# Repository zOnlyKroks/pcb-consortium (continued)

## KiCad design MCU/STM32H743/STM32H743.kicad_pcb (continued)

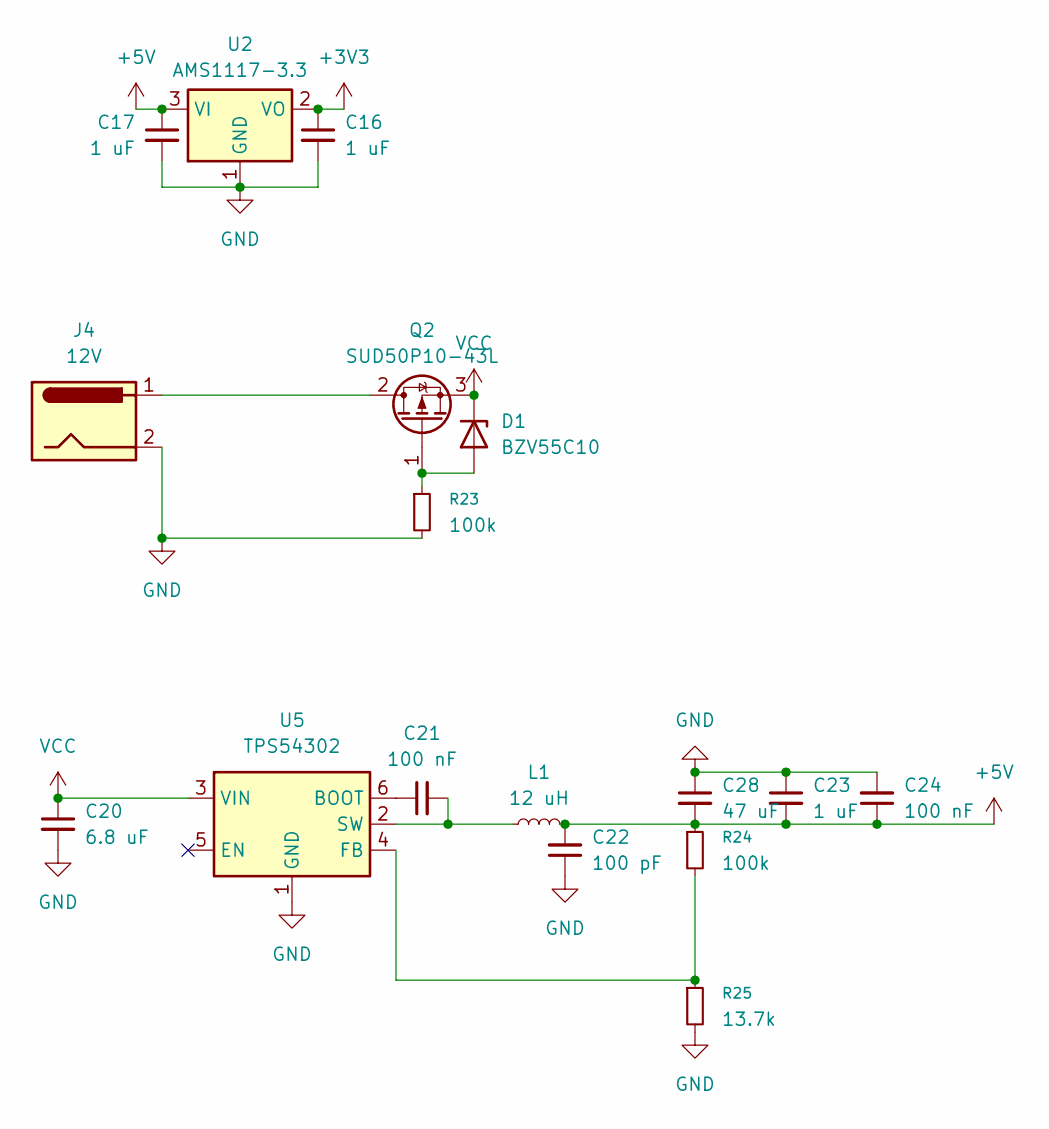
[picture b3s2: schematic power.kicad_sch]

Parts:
C16, C17, C23: 1 uF; C_0402_1005Metric
C20: 6.8 uF; C_0805_2012Metric
C21, C24: 100 nF; C_0402_1005Metric
C22: 100 pF; C_0402_1005Metric
C28: 47 uF; C_1206_3216Metric
D1: BZV55C10; D_MiniMELF
J4: 12V; BarrelJack_CUI_PJ-063AH_Horizontal
L1: 12 uH; L_0805_2012Metric
Q2: SUD50P10-43L; TO-252-2
R23, R24: 100k; R_0603_1608Metric
R25: 13.7k; R_0603_1608Metric
U2: AMS1117-3.3; SOT-223-3_TabPin2
U5: TPS54302; SOT-23-6

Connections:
+3V3: C16.1, U2.2 (VO); also elsewhere on the board
+5V: C17.1, C22.2, C23.2, C24.1, C28.2, L1.2, R24.1, U2.3 (VI); also elsewhere on the board
GND: C16.2, C17.2, C20.2, C22.1, C23.1, C24.2, C28.1, J4.2, R23.2, R25.2, U2.1 (GND), U5.1 (GND); also elsewhere on the board
unnamed: D1.2 (A), Q2.1 (G), R23.1
unnamed: J4.1, Q2.2 (D)
unnamed: C21.1, U5.6 (BOOT)
unnamed: R24.2, R25.1, U5.4 (FB)
unnamed: C21.2, L1.1, U5.2 (SW)
VCC: C20.1, D1.1 (K), Q2.3 (S), U5.3 (VIN)

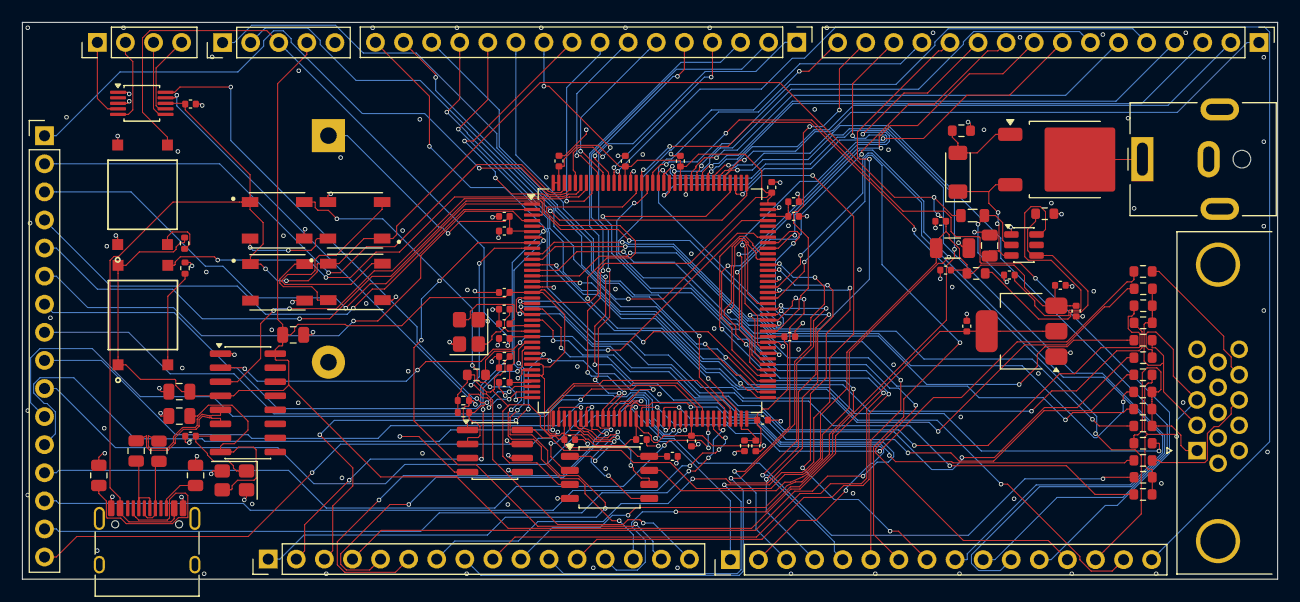
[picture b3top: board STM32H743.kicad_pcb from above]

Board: 4 copper layers, 113.5 x 50.3 mm, 91 parts (1 on the bottom side), 145 nets.

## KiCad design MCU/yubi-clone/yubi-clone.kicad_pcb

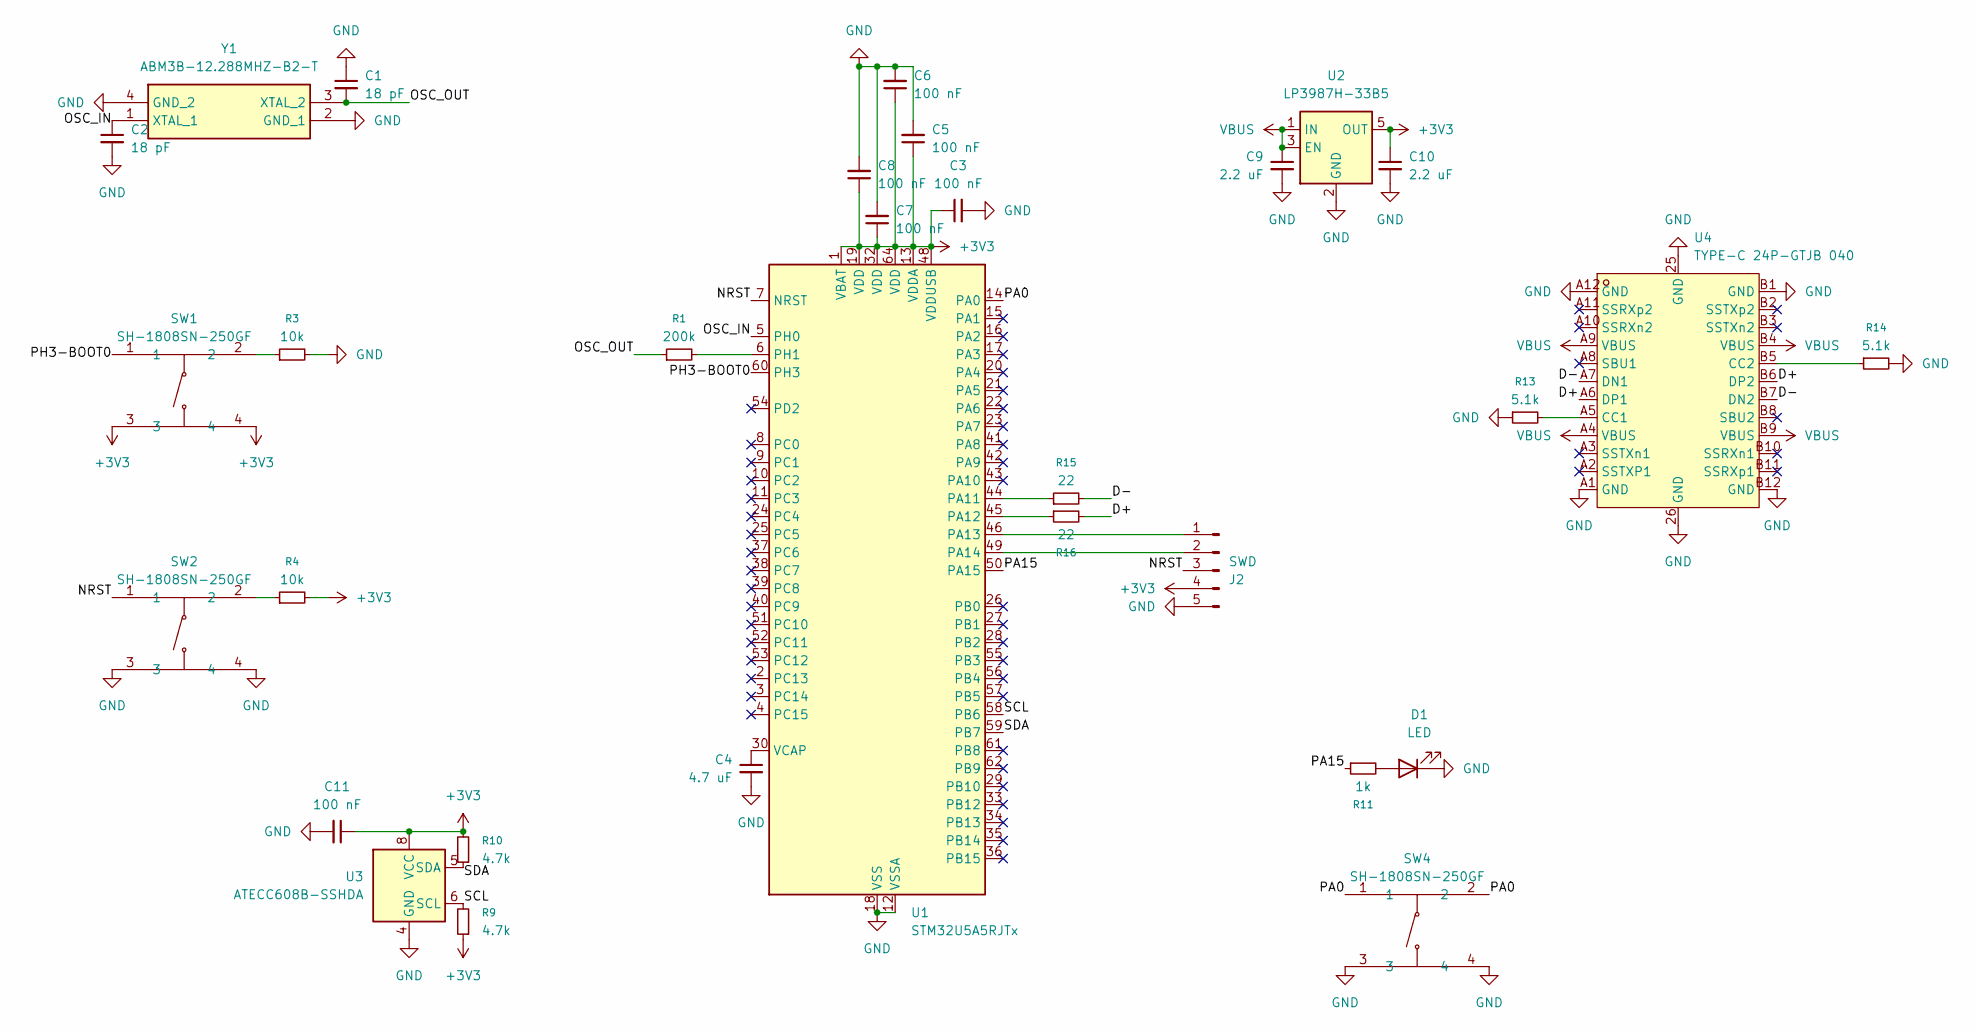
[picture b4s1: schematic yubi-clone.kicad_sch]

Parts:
C1, C2: 18 pF; C_0603_1608Metric
C3, C5, C6, C7, C8, C11: 100 nF; C_0603_1608Metric
C4: 4.7 uF; C_0603_1608Metric
C9, C10: 2.2 uF; C_0603_1608Metric
D1: LED; LED_0603_1608Metric
J2: SWD; PinHeader_1x05_P2.54mm_Vertical
R1: 200k; R_0603_1608Metric
R3, R4: 10k; R_0603_1608Metric
R9, R10: 4.7k; R_0603_1608Metric
R11: 1k; R_0603_1608Metric
R13, R14: 5.1k; R_0603_1608Metric
R15, R16: 22; R_0603_1608Metric
SW1, SW2, SW4: SH-1808SN-250GF; SW-SMD_4P-L4.2-W3.4-P2.15-LS5.2; MPN SH-1808SN-250gf; LCSC Part C52092028
U1: STM32U5A5RJTx; LQFP-64_10x10mm_P0.5mm
U2: LP3987H-33B5; SOT-23-5
U3: ATECC608B-SSHDA; SOIC-8_3.9x4.9mm_P1.27mm
U4: TYPE-C 24P-GTJB 040; USB-C-SMD_TYPE-C-24P-GTJB-040; MPN TYPE-C 24P-GTJB 040; LCSC Part C3151751
Y1: ABM3B-12.288MHZ-B2-T; ABM3B; Mouser Part Number 815-ABM3B-12.288-B2T

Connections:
+3V3: C3.1, C5.1, C6.1, C7.1, C8.1, C10.1, C11.1, J2.4, R4.2, R9.1, R10.2, SW1.3, SW1.4, U1.1 (VBAT), U1.13 (VDDA), U1.19 (VDD), U1.32 (VDD), U1.48 (VDDUSB), U1.64 (VDD), U2.5 (OUT), U3.8 (VCC)
/D+: R16.2, U4.A6 (DP1), U4.B6 (DP2)
/D-: R15.2, U4.A7 (DN1), U4.B7 (DN2)
/NRST: J2.3, SW2.1, U1.7 (NRST)
/OSC_IN: C2.1, U1.5 (PH0), Y1.1 (XTAL_1)
/OSC_OUT: C1.2, R1.1, Y1.3 (XTAL_2)
/PA0: SW4.1, SW4.2, U1.14 (PA0)
/PA15: R11.1, U1.50 (PA15)
/PH3-BOOT0: SW1.1, U1.60 (PH3)
/SCL: R9.2, U1.58 (PB6), U3.6 (SCL)
/SDA: R10.1, U1.59 (PB7), U3.5 (SDA)
GND: C1.1, C2.2, C3.2, C4.2, C5.2, C6.2, C7.2, C8.2, C9.2, C10.2, C11.2, D1.1 (K), J2.5, R3.2, R13.1, R14.2, SW2.3, SW2.4, SW4.3, SW4.4, U1.12 (VSSA), U1.18 (VSS), U1.31 (VSS), U1.47 (VSS), U1.63 (VSS), U2.2 (GND), U3.4 (GND), U4.25 (GND), U4.26 (GND), U4.A1 (GND), U4.A12 (GND), U4.B1 (GND), U4.B12 (GND), Y1.2 (GND_1), Y1.4 (GND_2)
unnamed: D1.2 (A), R11.2
unnamed: J2.1, U1.46 (PA13)
unnamed: J2.2, U1.49 (PA14)
unnamed: R3.1, SW1.2
unnamed: R4.1, SW2.2
unnamed: R15.1, U1.44 (PA11)
unnamed: R16.1, U1.45 (PA12)
unnamed: R1.2, U1.6 (PH1)
unnamed: C4.1, U1.30 (VCAP)
unnamed: R13.2, U4.A5 (CC1)
unnamed: R14.1, U4.B5 (CC2)
VBUS: C9.1, U2.1 (IN), U2.3 (EN), U4.A4 (VBUS), U4.A9 (VBUS), U4.B4 (VBUS), U4.B9 (VBUS)

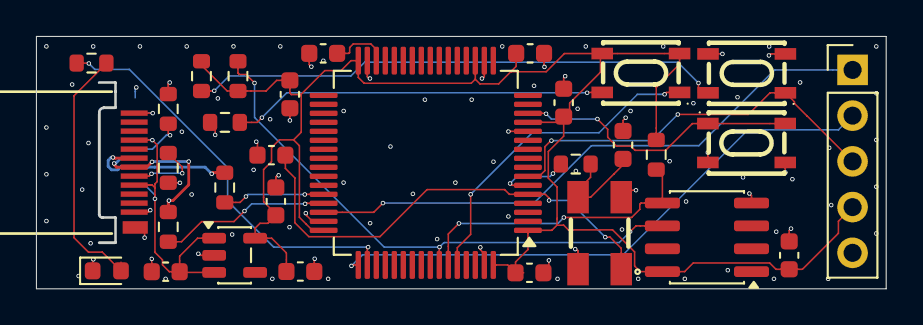
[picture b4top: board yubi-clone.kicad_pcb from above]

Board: 4 copper layers, 47.2 x 14.0 mm, 31 parts (0 on the bottom side), 24 nets.

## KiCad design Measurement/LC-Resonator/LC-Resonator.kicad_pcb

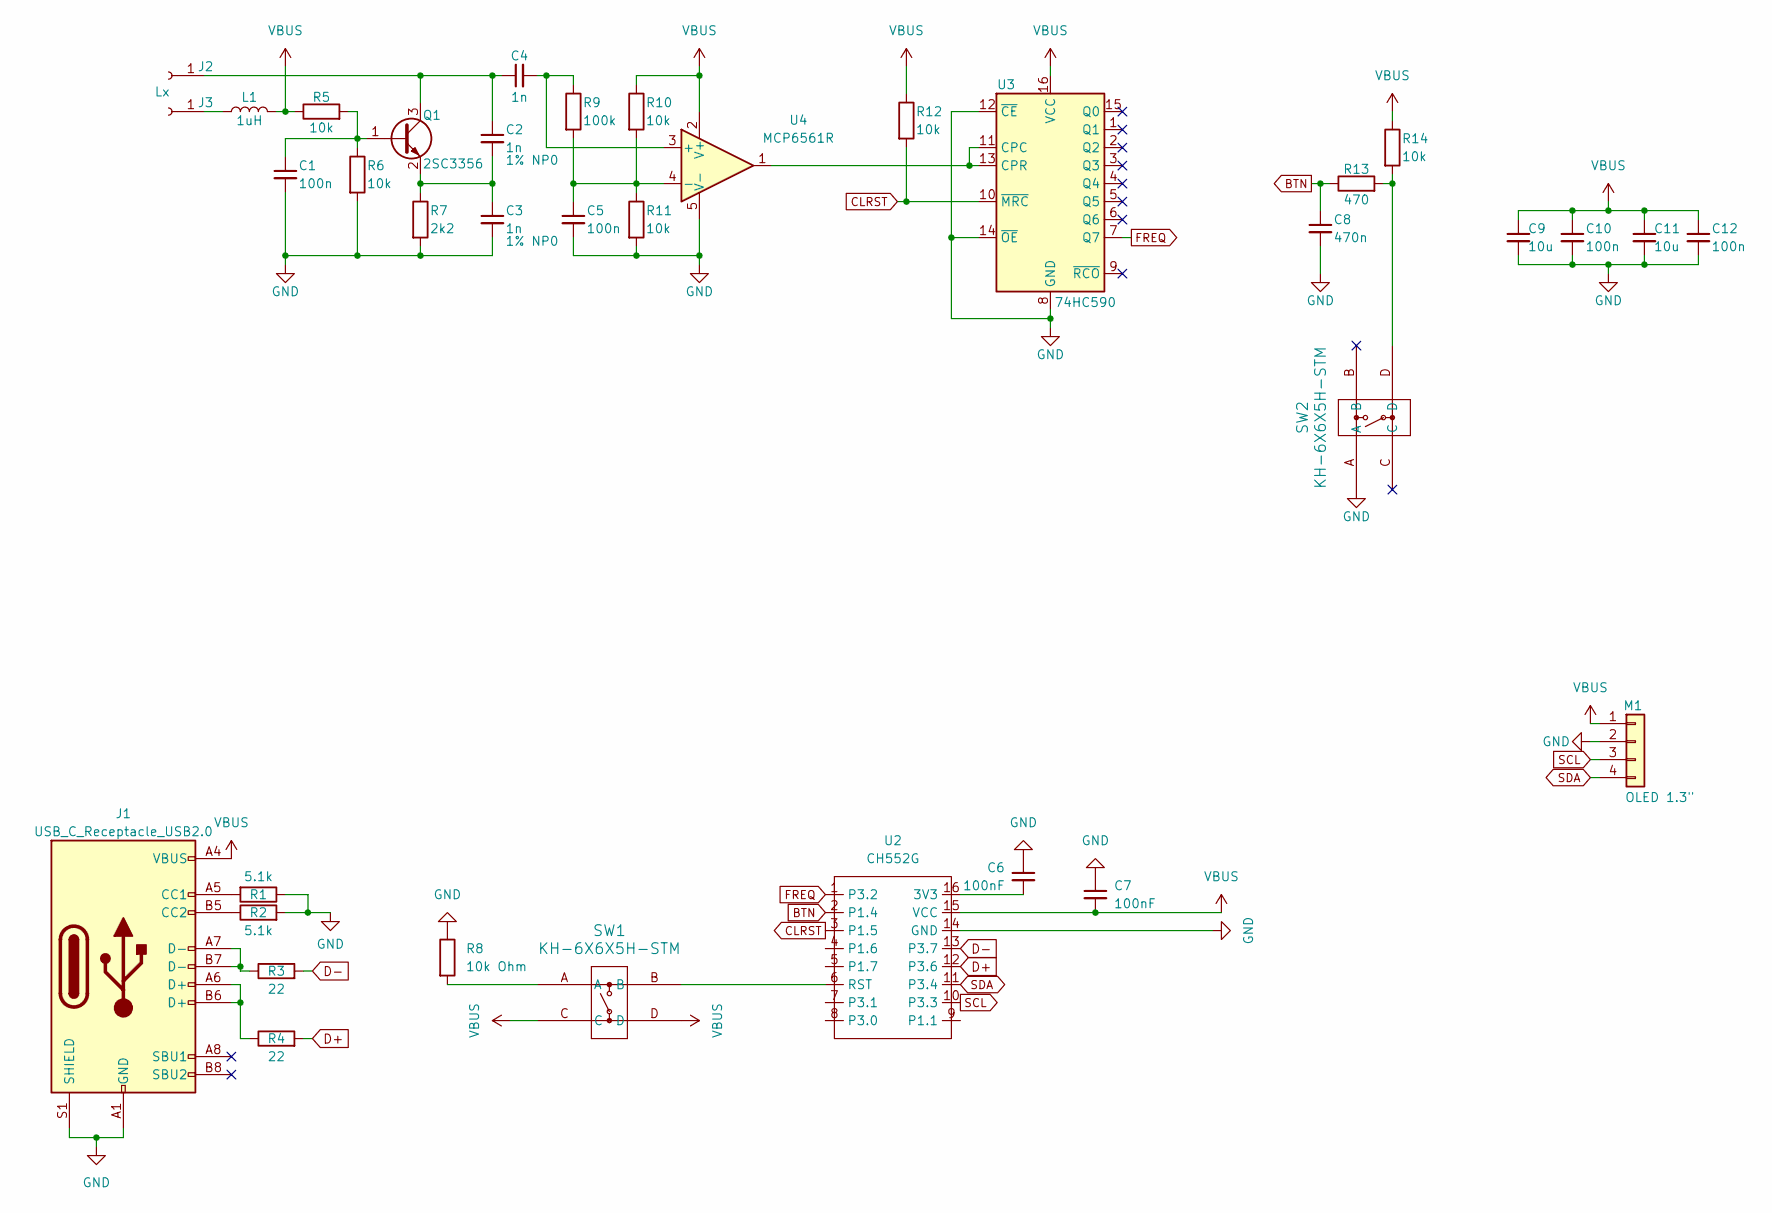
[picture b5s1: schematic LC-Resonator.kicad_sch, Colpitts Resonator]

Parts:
C1, C5, C10, C12: 100n; C_0603_1608Metric; LCSC C14663
C2, C3: 1n; C_0603_1608Metric; LCSC C309468
C4: 1n; C_0603_1608Metric; LCSC C1588
C6, C7: 100nF; C_0805_2012Metric; LCSC Part # C49678
C8: 470n; C_0603_1608Metric; LCSC C1623
C9, C11: 10u; C_0603_1608Metric; LCSC C19702
J1: USB_C_Receptacle_USB2.0; USB_C_Receptacle_HRO_TYPE-C-31-M-12; JlcRotOffset 180
J2, J3: Lx; 4mm_Banana_Socket_Deltron_571; LCSC C7437325
L1: 1uH; L_0805_2012Metric; LCSC C113100
M1: OLED 1.3"; LCD_OLED_128X64_1.3_I2C; LCSC C7465997
Q1: 2SC3356; SOT-23; LCSC C28646266
R1, R2: 5.1k; R_0603_1608Metric; LCSC Part # C23186
R3, R4: 22; R_0603_1608Metric; LCSC Part # C23345
R5, R6, R10, R11, R12, R14: 10k; R_0603_1608Metric; LCSC C25804
R7: 2k2; R_0603_1608Metric; LCSC C4190
R8: 10k Ohm; R_0805_2012Metric; LCSC Part # C17414
R9: 100k; R_0603_1608Metric; LCSC C25803
R13: 470; R_0603_1608Metric; LCSC C23179
SW1, SW2: KH-6X6X5H-STM; KH-6X6X5H-STM_SKE; LCSC Part # C2837531
U2: CH552G; LCSC Part # C111292
U3: 74HC590; SOIC-16_3.9x9.9mm_P1.27mm; LCSC C547118
U4: MCP6561R; SOT-23-5; LCSC Part # C250337

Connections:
BTN: C8.1, R13.1, U2.2 (P1.4)
CLRST: R12.2, U2.3 (P1.5), U3.10 (~MRC)
D+: R4.2, U2.12 (P3.6)
D-: R3.2, U2.13 (P3.7)
FREQ: U2.1 (P3.2), U3.7 (Q7)
GND: C1.2, C3.2, C5.2, C6.1, C7.1, C8.2, C9.2, C10.2, C11.2, C12.2, J1.A1 (GND), J1.A12 (GND), J1.B1 (GND), J1.B12 (GND), J1.S1 (SHIELD), M1.2, R1.1, R2.2, R6.2, R7.2, R8.1, R11.2, SW2.A, U2.14 (GND), U3.8 (GND), U3.12 (~CE), U3.14 (~OE), U4.5 (V-)
unnamed: J1.A5 (CC1), R1.2
unnamed: J1.B5 (CC2), R2.1
unnamed: J1.A6 (D+), J1.B6 (D+), R4.1
unnamed: J1.A7 (D-), J1.B7 (D-), R3.1
unnamed: C2.1, C4.1, J2.1, Q1.3 (C)
unnamed: J3.1, L1.1
unnamed: C1.1, Q1.1 (B), R5.2, R6.1
unnamed: C2.2, C3.1, Q1.2 (E), R7.1
unnamed: R8.2, SW1.A
unnamed: R13.2, R14.2, SW2.D
unnamed: C6.2, U2.16 (3V3)
unnamed: SW1.B, U2.6 (RST)
unnamed: U3.11 (CPC), U3.13 (CPR), U4.1
unnamed: C4.2, R9.1, U4.3 (+)
unnamed: C5.1, R9.2, R10.2, R11.1, U4.4 (-)
SCL: M1.3, U2.10 (P3.3)
SDA: M1.4, U2.11 (P3.4)
VBUS: C7.2, C9.1, C10.1, C11.1, C12.1, J1.A4 (VBUS), J1.A9 (VBUS), J1.B4 (VBUS), J1.B9 (VBUS), L1.2, M1.1, R5.1, R10.1, R12.1, R14.1, SW1.C, SW1.D, U2.15 (VCC), U3.16 (VCC), U4.2 (V+)

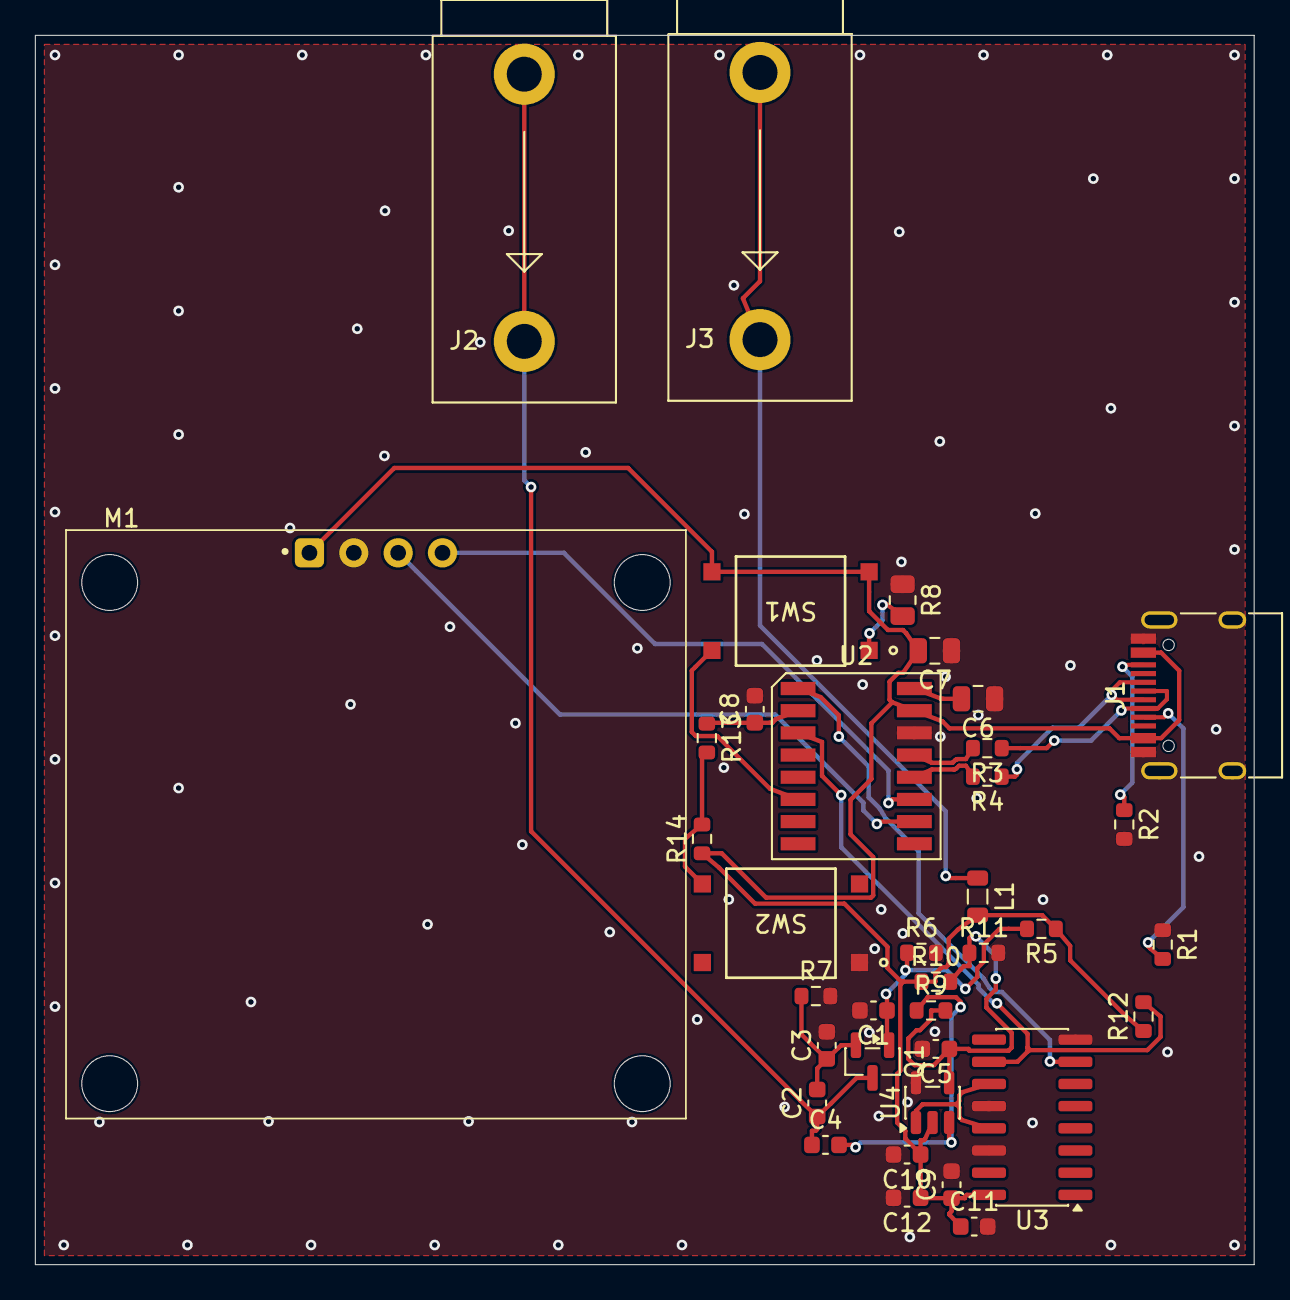
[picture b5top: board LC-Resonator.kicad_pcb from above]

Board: 2 copper layers, 69.8 x 70.4 mm, 37 parts (0 on the bottom side), 24 nets.

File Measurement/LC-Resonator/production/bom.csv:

Designator,Footprint,Quantity,Value,LCSC Part #
"C1, C10, C12, C5",0603,4,100n,C14663
"C11, C9",0603,2,10u,C19702
"C2, C3",0603,2,1n,C309468
C4,0603,1,1n,C1588
"C6, C7",0805,2,100nF,C49678
C8,0603,1,470n,C1623
J1,USB_C_Receptacle_HRO_TYPE-C-31-M-12,1,USB_C_Receptacle_USB2.0,C165948
"J2, J3",4mm_Banana_Socket_Deltron_571,2,Lx,C7437325
L1,0805,1,1uH,C113100
M1,LCD_OLED_128X64_1.3_I2C,1,"OLED 1.3""",C7465997
Q1,SOT-23,1,2SC3356,C28646266
"R1, R2",0603,2,5.1k,C23186
"R10, R11, R12, R14, R5, R6",0603,6,10k,C25804
R13,0603,1,470,C23179
"R3, R4",0603,2,22,C23345
R7,0603,1,2k2,C4190
R8,0805,1,10k Ohm,C17414
R9,0603,1,100k,C25803
"SW1, SW2",KH-6X6X5H-STM_SKE,2,KH-6X6X5H-STM,C2837531
U2,CH552G,1,CH552G,C111292
U3,SOIC-16_3.9x9.9mm_P1.27mm,1,74HC590,C547118
U4,SOT-23-5,1,MCP6561R,C250337

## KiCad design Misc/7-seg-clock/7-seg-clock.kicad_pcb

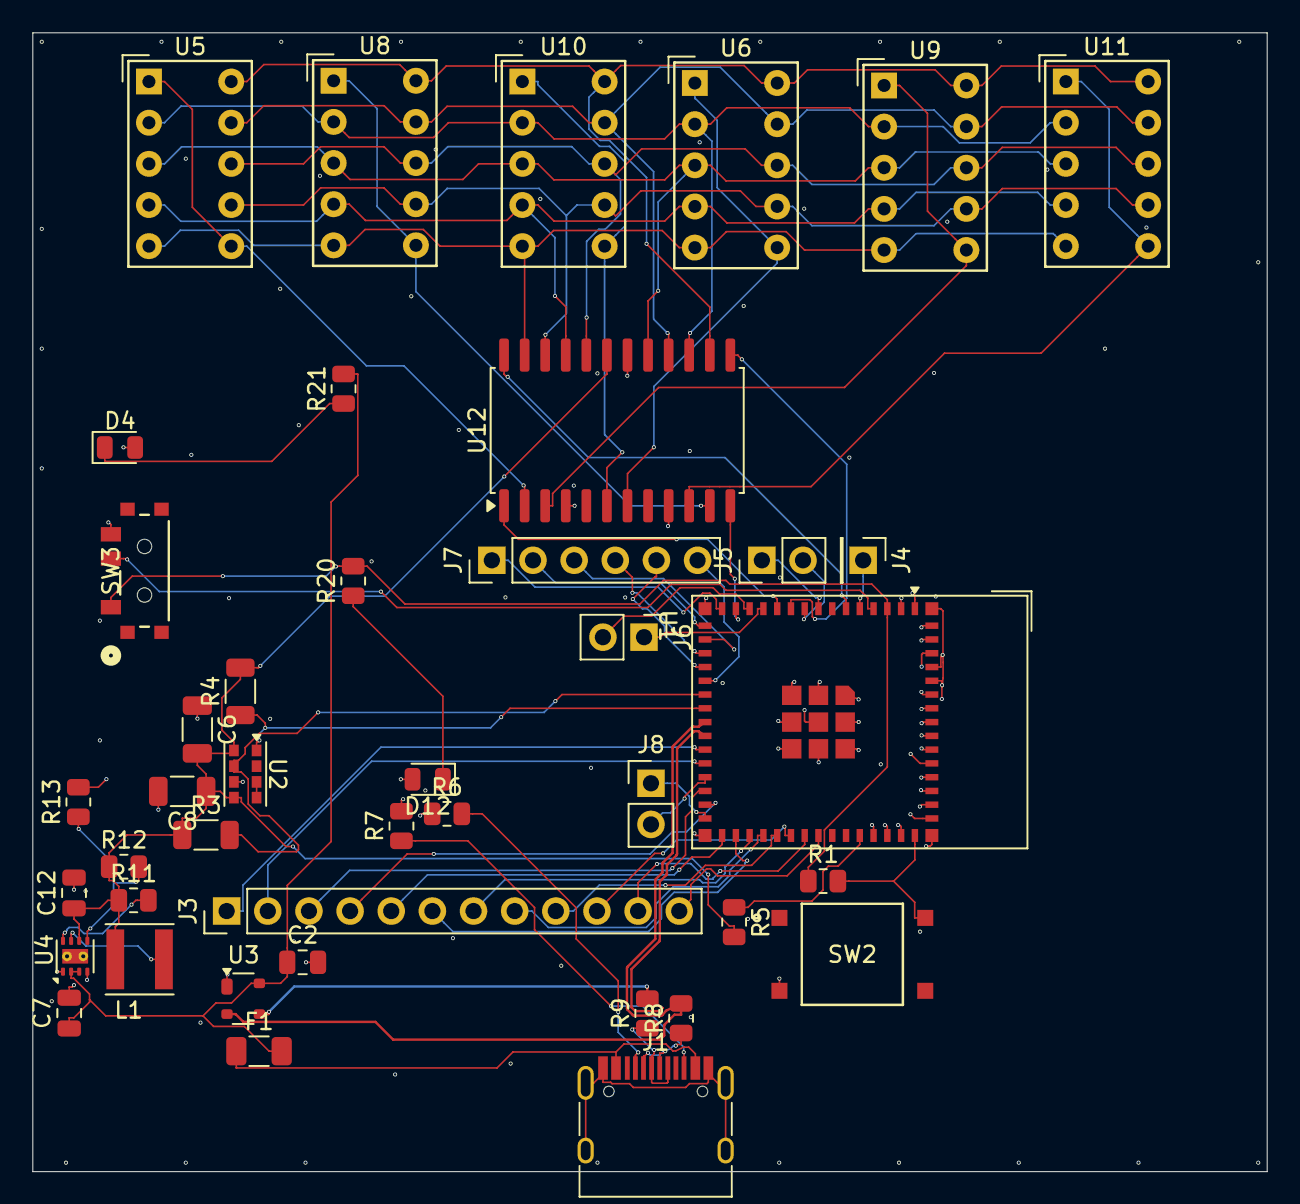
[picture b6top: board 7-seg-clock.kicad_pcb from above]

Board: 4 copper layers, 76.2 x 70.3 mm, 42 parts (0 on the bottom side), 66 nets.

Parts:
C2: 100nF; C_0805_2012Metric
C6, C8: 1 uF; C_1206_3216Metric
C7: 10 uF; C_0805_2012Metric
C12: 22 uF; C_0805_2012Metric
D4: 5V LED; LED_0805_2012Metric
D12: 3.3V LED; LED_0805_2012Metric
F1: 500 mA; Fuse_1206_3216Metric
J1: USB_C_Receptacle_USB2.0; USB_C_Receptacle_HRO_TYPE-C-31-M-12
J3: Conn_01x12_Pin; PinHeader_1x12_P2.54mm_Vertical
J4: Conn_01x01_Pin; PinHeader_1x01_P2.54mm_Vertical
J5, J6, J8: Conn_01x02_Pin; PinHeader_1x02_P2.54mm_Vertical
J7: Conn_01x06_Pin; PinHeader_1x06_P2.54mm_Vertical
L1: 2.2 uH; IND_PA4332.222NLT
R1, R5: 10k; R_0805_2012Metric
R3, R4: 4.7k; R_1206_3216Metric
R6, R7: 5.1k; R_0805_2012Metric
R8, R9: 22; R_0805_2012Metric
R11: 100k; R_0805_2012Metric
R12: 562kΩ; R_0805_2012Metric
R13: 180kΩ; R_0805_2012Metric
R20: 150; R_0805_2012Metric
R21: 330; R_0805_2012Metric
SW2: EN; KH-6X6X5H-STM_SKE
SW3: SLW-66527511-SMT-TR; SLW-66527511-SMT-TR_CUD
U1: ESP32-S3-MINI-1; ESP32-S2-MINI-1
U2: APDS-9960; Avago_APDS-9960
U3: PRTR5V0U2X; SOT-143
U4: TPS62160DSG; WSON-8-1EP_2x2mm_P0.5mm_EP0.9x1.6mm_ThermalVias
U5, U6, U8, U9, U10, U11: HDSP-7501; HDSP-A151
U12: MAX7221xWG; SOIC-24W_7.5x15.4mm_P1.27mm

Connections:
+3.3V: C6.2, C8.1, C12.1, L1.2, R3.1, R4.2, R5.2, R11.1, R12.1, U2.5 (LED_A), U2.8 (VDD), U4.6 (VOS), U12.19 (V+)
+3V3: R1.1, R20.2, SW3.1, U1.3 (3V3)
+5V: C2.1, C7.1, F1.2, R21.2, U3.4 (VCC), U4.2 (VIN), U4.3 (EN)
/0: U5.1 (CA), U5.6 (CA), U12.2 (DIG_0)
/1: U8.1 (CA), U8.6 (CA), U12.11 (DIG_1)
/2: U10.1 (CA), U10.6 (CA), U12.6 (DIG_2)
/3: U6.1 (CA), U6.6 (CA), U12.7 (DIG_3)
/4: U9.1 (CA), U9.6 (CA), U12.3 (DIG_4)
/5: U11.1 (CA), U11.6 (CA), U12.10 (DIG_5)
/A: U5.10 (A), U6.10 (A), U8.10 (A), U9.10 (A), U10.10 (A), U11.10 (A), U12.14 (SEG_A)
/B: U5.9 (B), U6.9 (B), U8.9 (B), U9.9 (B), U10.9 (B), U11.9 (B), U12.16 (SEG_B)
/BOOTMODE: SW3.2, U1.4 (IO0)
/C: U5.8 (C), U6.8 (C), U8.8 (C), U9.8 (C), U10.8 (C), U11.8 (C), U12.20 (SEG_C)
/D: U5.5 (D), U6.5 (D), U8.5 (D), U9.5 (D), U10.5 (D), U11.5 (D), U12.23 (SEG_D)
/DP: U5.7 (DP), U6.7 (DP), U8.7 (DP), U9.7 (DP), U10.7 (DP), U11.7 (DP), U12.22 (SEG_DP)
/E: U5.4 (E), U6.4 (E), U8.4 (E), U9.4 (E), U10.4 (E), U11.4 (E), U12.21 (SEG_E)
/F: U5.2 (F), U6.2 (F), U8.2 (F), U9.2 (F), U10.2 (F), U11.2 (F), U12.15 (SEG_F)
/G: U5.3 (G), U6.3 (G), U8.3 (G), U9.3 (G), U10.3 (G), U11.3 (G), U12.17 (SEG_G)
/I2C1_SCL: R3.2, U1.21 (IO17), U2.7 (SCL)
/I2C1_SDA: R4.1, U1.22 (IO18), U2.1 (SDA)
/SPI1_CLK: U1.10 (IO6), U12.13 (CLK)
/SPI1_CS: U1.14 (IO10), U12.12 (~CS)
/SPI1_MISO: U1.6 (IO2), U12.24 (DOUT)
/SPI1_MOSI: U1.11 (IO7), U12.1 (DIN)
D+: R9.2, U1.24 (USB_D+), U3.3 (I/O2)
D-: R8.2, U1.23 (USB_D-), U3.2 (I/O1)
GND: C2.2, C6.1, C7.2, C8.2, C12.2, D4.2 (A), D12.2 (A), R6.1, R7.2, R13.2, SW2.C, SW3.3, U1.1 (GND), U1.2 (GND), U1.42 (GND), U1.43 (GND), U1.44 (IO46), U1.46 (GND), U1.47 (GND), U1.48 (GND), U1.49 (GND), U1.50 (GND), U1.51 (GND), U1.52 (GND), U1.53 (GND), U1.54 (GND), U1.55 (GND), U1.56 (GND), U1.57 (GND), U1.58 (GND), U1.59 (GND), U1.60 (GND), U1.61 (GND), U1.62 (GND), U1.63 (GND), U1.64 (GND), U1.65 (GND), U2.6 (GND), U3.1 (GND), U4.1 (PGND), U4.4 (AGND), U4.9 (PAD), U12.4 (GND), U12.9 (GND), U12.18 (ISET)
unnamed: D4.1 (K), R21.1
unnamed: D12.1 (K), R20.1
unnamed: J1.A5 (CC1), R6.2
unnamed: J1.B5 (CC2), R7.1
unnamed: J1.A6 (D+), J1.B6 (D+), R9.1
unnamed: J1.A7 (D-), J1.B7 (D-), R8.1
unnamed: J1.A1 (GND), J1.A12 (GND), J1.B1 (GND), J1.B12 (GND), J1.S1 (SHIELD)
unnamed: J3.1, U1.25 (IO21)
unnamed: J3.2, U1.26 (IO26)
unnamed: J3.3, U1.28 (IO33)
unnamed: J3.4, U1.29 (IO34)
unnamed: J3.5, U1.31 (IO35)
unnamed: J3.6, U1.32 (IO36)
unnamed: J3.7, U1.33 (IO37)
unnamed: J3.8, U1.34 (IO38)
unnamed: J3.9, U1.35 (IO39)
unnamed: J3.10, U1.36 (IO40)
unnamed: J3.11, U1.37 (IO41)
unnamed: J3.12, U1.38 (IO42)
unnamed: J4.1, U1.5 (IO1)
unnamed: J5.1, U1.8 (IO4)
unnamed: J5.2, U1.9 (IO5)
unnamed: J6.1, U1.12 (IO8)
unnamed: J6.2, U1.13 (IO9)
unnamed: J7.1, U1.15 (IO11)
unnamed: J7.2, U1.16 (IO12)
unnamed: J7.3, U1.17 (IO13)
unnamed: J7.4, U1.18 (IO14)
unnamed: J7.5, U1.19 (IO15)
unnamed: J7.6, U1.20 (IO16)
unnamed: J8.1, U1.30 (IO48)
unnamed: J8.2, U1.27 (IO47)
unnamed: R1.2, SW2.B, U1.45 (EN)
unnamed: R5.1, U1.41 (IO45)
unnamed: U2.3 (LDR), U2.4 (LED_K)
unnamed: R12.2, R13.1, U4.5 (FB)
unnamed: R11.2, U4.8 (PG)
unnamed: L1.1, U4.7 (SW)
VBUS: F1.1, J1.A4 (VBUS), J1.A9 (VBUS), J1.B4 (VBUS), J1.B9 (VBUS)

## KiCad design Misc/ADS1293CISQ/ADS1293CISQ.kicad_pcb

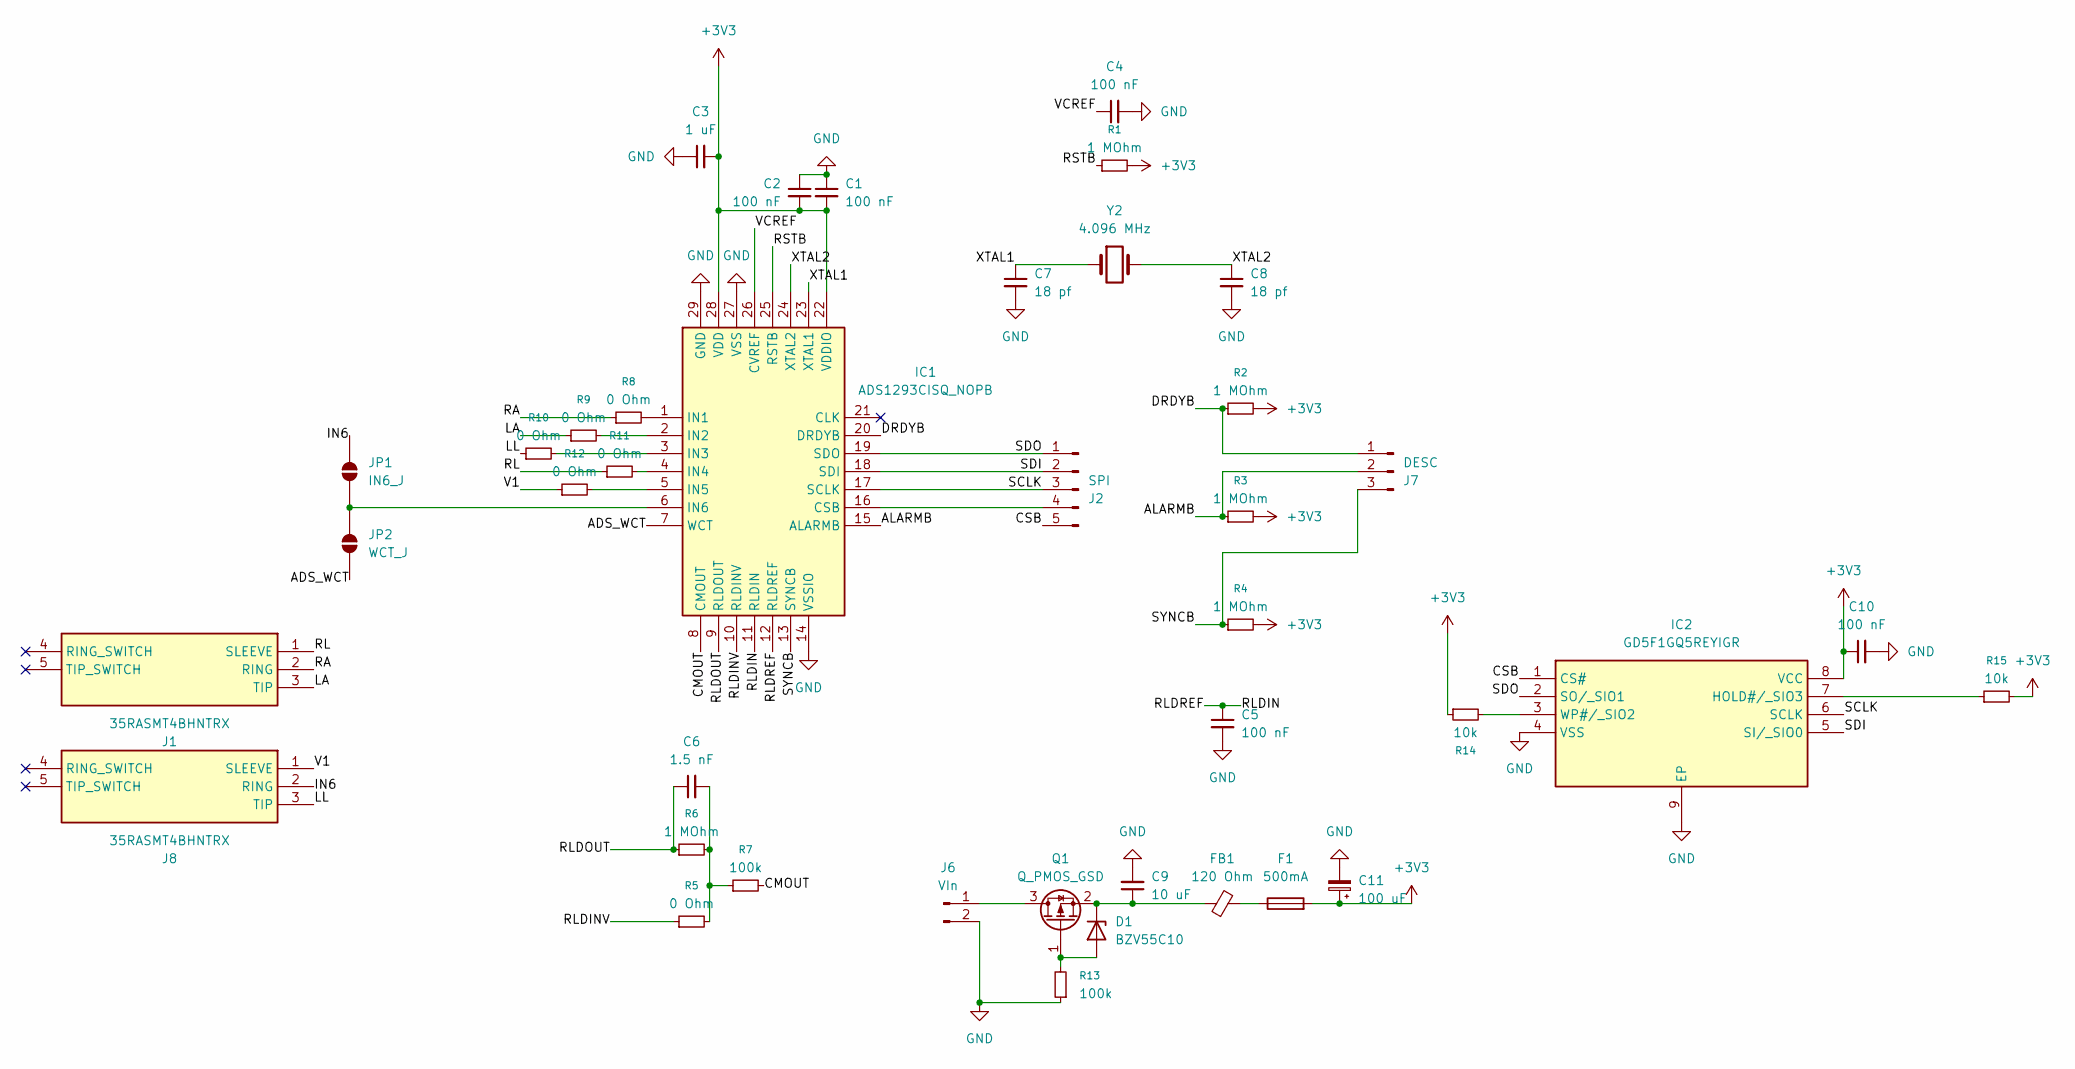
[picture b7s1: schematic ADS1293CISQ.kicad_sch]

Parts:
C1, C2, C4, C5, C10: 100 nF; C_0402_1005Metric
C3: 1 uF; C_0402_1005Metric
C6: 1.5 nF; C_0402_1005Metric
C7, C8: 18 pf; C_0402_1005Metric
C9: 10 uF; C_0805_2012Metric
C11: 100 uF; CP_EIA-3216-18_Kemet-A
D1: BZV55C10; D_MiniMELF
F1: 500mA; Fuse_0805_2012Metric
FB1: 120 Ohm; R_0402_1005Metric
IC1: ADS1293CISQ_NOPB; QFN50P500X500X80-29N; Mouser Part Number 595-ADS1293CISQNPB
IC2: GD5F1GQ5REYIGR; SON127P800X600X80-9N-D; Manufacturer_Part_Number GD5F1GQ5REYIGR
J1, J8: 35RASMT4BHNTRX; Mouser Part Number 502-35RASMT4BHNTRX
J2: SPI; PinHeader_1x05_P2.54mm_Vertical
J6: VIn; PinHeader_1x02_P2.54mm_Vertical
J7: DESC; PinHeader_1x03_P2.54mm_Vertical
JP1: IN6_J; SolderJumper-2_P1.3mm_Open_Pad1.0x1.5mm
JP2: WCT_J; SolderJumper-2_P1.3mm_Open_Pad1.0x1.5mm
Q1: Q_PMOS_GSD; SOT-23
R1, R2, R3, R4, R6: 1 MOhm; R_0402_1005Metric
R5, R8, R9, R10, R11, R12: 0 Ohm; R_0402_1005Metric
R7, R13: 100k; R_0402_1005Metric
R14, R15: 10k; R_0402_1005Metric
Y2: 4.096 MHz; Crystal_SMD_HC49-SD

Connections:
+3V3: C1.2, C2.2, C3.2, C10.1, C11.1, F1.2, IC1.22 (VDDIO), IC1.28 (VDD), IC2.8 (VCC), R1.2, R2.2, R3.2, R4.2, R14.1, R15.2
/ADS_WCT: IC1.7 (WCT), JP2.1 (A)
/ALARMB: IC1.15 (ALARMB), J7.2, R3.1
/CMOUT: IC1.8 (CMOUT), R7.2
/CSB: IC2.1 (CS#), J2.5
/DRDYB: IC1.20 (DRDYB), J7.1, R2.1
/IN6: J8.2 (RING), JP1.2 (B)
/LA: J1.3 (TIP), R9.1
/LL: J8.3 (TIP), R10.1
/RA: J1.2 (RING), R8.1
/RL: J1.1 (SLEEVE), R11.1
/RLDIN: C5.1, IC1.11 (RLDIN), IC1.12 (RLDREF)
/RLDINV: IC1.10 (RLDINV), R5.1
/RLDOUT: C6.1, IC1.9 (RLDOUT), R6.1
/RSTB: IC1.25 (RSTB), R1.1
/SCLK: IC1.17 (SCLK), IC2.6 (SCLK), J2.3
/SDI: IC1.18 (SDI), IC2.5 (SI/_SIO0), J2.2
/SDO: IC1.19 (SDO), IC2.2 (SO/_SIO1), J2.1
/SYNCB: IC1.13 (SYNCB), J7.3, R4.1
/V1: J8.1 (SLEEVE), R12.1
/VCREF: C4.1, IC1.26 (CVREF)
/XTAL1: C7.1, IC1.23 (XTAL1), Y2.1
/XTAL2: C8.1, IC1.24 (XTAL2), Y2.2
GND: C1.1, C2.1, C3.1, C4.2, C5.2, C7.2, C8.2, C9.2, C10.2, C11.2, IC1.14 (VSSIO), IC1.27 (VSS), IC1.29 (GND), IC2.4 (VSS), IC2.9 (EP), J6.2, R13.1
unnamed: C6.2, R5.2, R6.2, R7.1
unnamed: D1.2 (A), Q1.1 (G), R13.2
unnamed: C9.1, D1.1 (K), FB1.1, Q1.2 (S)
unnamed: F1.1, FB1.2
unnamed: IC1.16 (CSB), J2.4
unnamed: IC1.1 (IN1), R8.2
unnamed: IC1.2 (IN2), R9.2
unnamed: IC1.3 (IN3), R10.2
unnamed: IC1.4 (IN4), R11.2
unnamed: IC1.5 (IN5), R12.2
unnamed: IC1.6 (IN6), JP1.1 (A), JP2.2 (B)
unnamed: IC2.7 (HOLD#/_SIO3), R15.1
unnamed: IC2.3 (WP#/_SIO2), R14.2
unnamed: J6.1, Q1.3 (D)

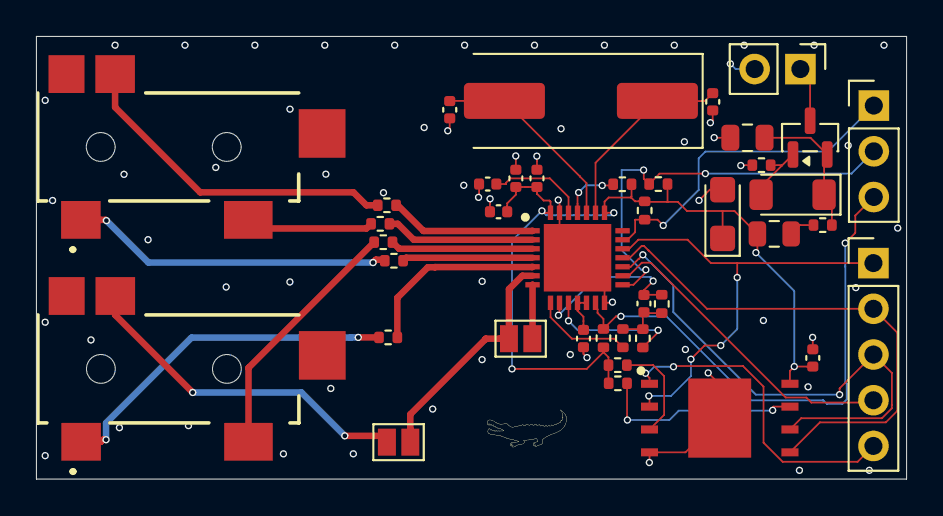
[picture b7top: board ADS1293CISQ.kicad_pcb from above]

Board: 4 copper layers, 48.3 x 24.6 mm, 40 parts (0 on the bottom side), 38 nets.
